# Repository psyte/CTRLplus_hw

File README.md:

# CTRLplus_hw
CTRLplus Eagle schematics and boards

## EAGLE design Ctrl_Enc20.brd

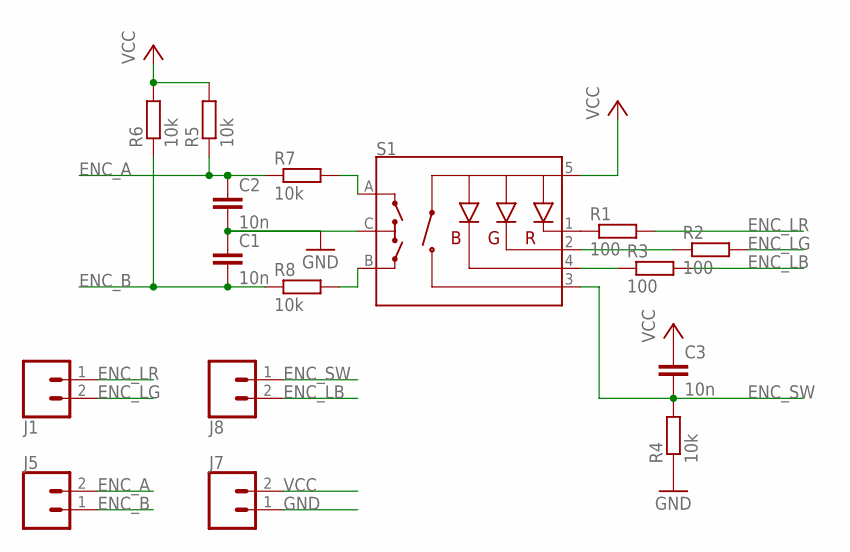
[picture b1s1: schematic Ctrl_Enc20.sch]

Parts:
C1, C2, C3: 10n; C0603
J1, J5, J7, J8: CONN_02; 1X02
R1, R2, R3: 100; R0603
R4, R5, R6, R7, R8: 10k; R0603
S1: ENCODER-RGB-SWITCH; ENCODER_LED_3

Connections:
ENC_A: C2.1, J5.2, R5.1, R7.1
ENC_B: C1.2, J5.1, R6.1, R8.1
ENC_LB: J8.2, R3.2
ENC_LG: J1.2, R2.2
ENC_LR: J1.1, R1.2
ENC_SW: C3.2, J8.1, R4.2, S1.3 (SW)
GND: C1.1, C2.2, J7.1, R4.1, S1.C
unnamed: R1.1, S1.1 (-R)
unnamed: R2.1, S1.2 (-G)
unnamed: R3.1, S1.4 (-B)
unnamed: R7.2, S1.A
unnamed: R8.2, S1.B
VCC: C3.1, J7.2, R5.2, R6.2, S1.5 (+)

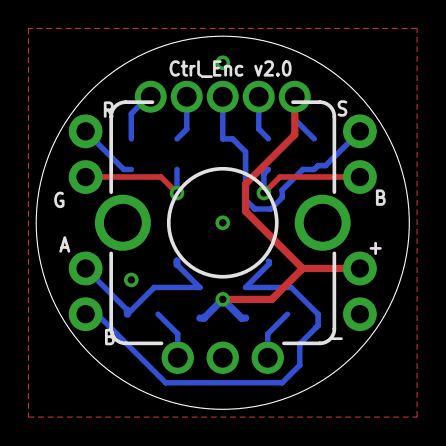
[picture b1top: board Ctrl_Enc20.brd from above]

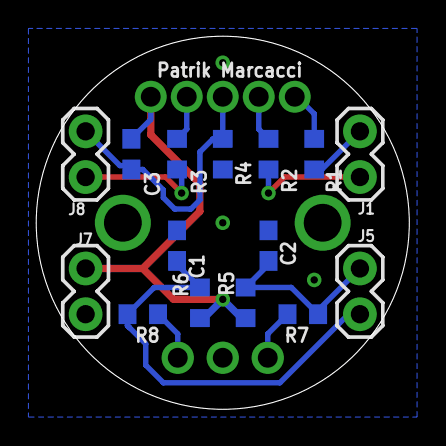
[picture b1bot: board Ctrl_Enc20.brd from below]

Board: 2 copper layers, 20.7 x 20.7 mm, 16 parts (15 on the bottom side), 13 nets.

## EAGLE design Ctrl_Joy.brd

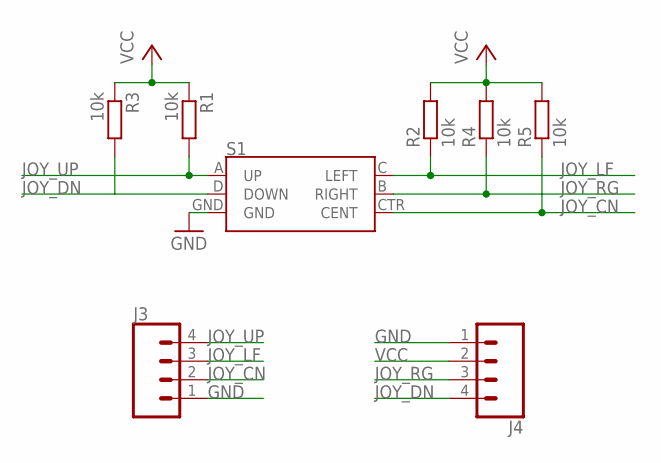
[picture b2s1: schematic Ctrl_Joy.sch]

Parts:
J3, J4: CONN_04; 1X04
R1, R2, R3, R4, R5: 10k; R0603
S1: JOYSTICK_MINI

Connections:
GND: J3.1, J4.1, S1.GND
JOY_CN: J3.2, R5.1, S1.CTR (CENT)
JOY_DN: J4.4, R3.2, S1.D (DOWN)
JOY_LF: J3.3, R2.1, S1.C (LEFT)
JOY_RG: J4.3, R4.1, S1.B (RIGHT)
JOY_UP: J3.4, R1.2, S1.A (UP)
VCC: J4.2, R1.1, R2.2, R3.1, R4.2, R5.2

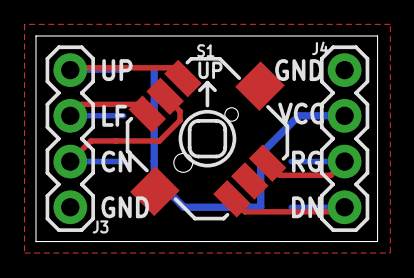
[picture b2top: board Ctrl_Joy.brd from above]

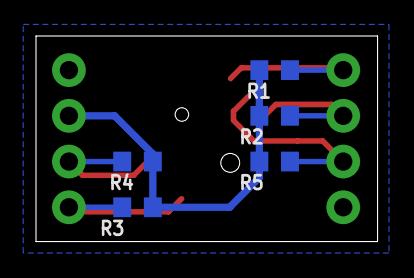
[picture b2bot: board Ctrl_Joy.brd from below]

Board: 2 copper layers, 19.0 x 11.4 mm, 8 parts (5 on the bottom side), 7 nets.

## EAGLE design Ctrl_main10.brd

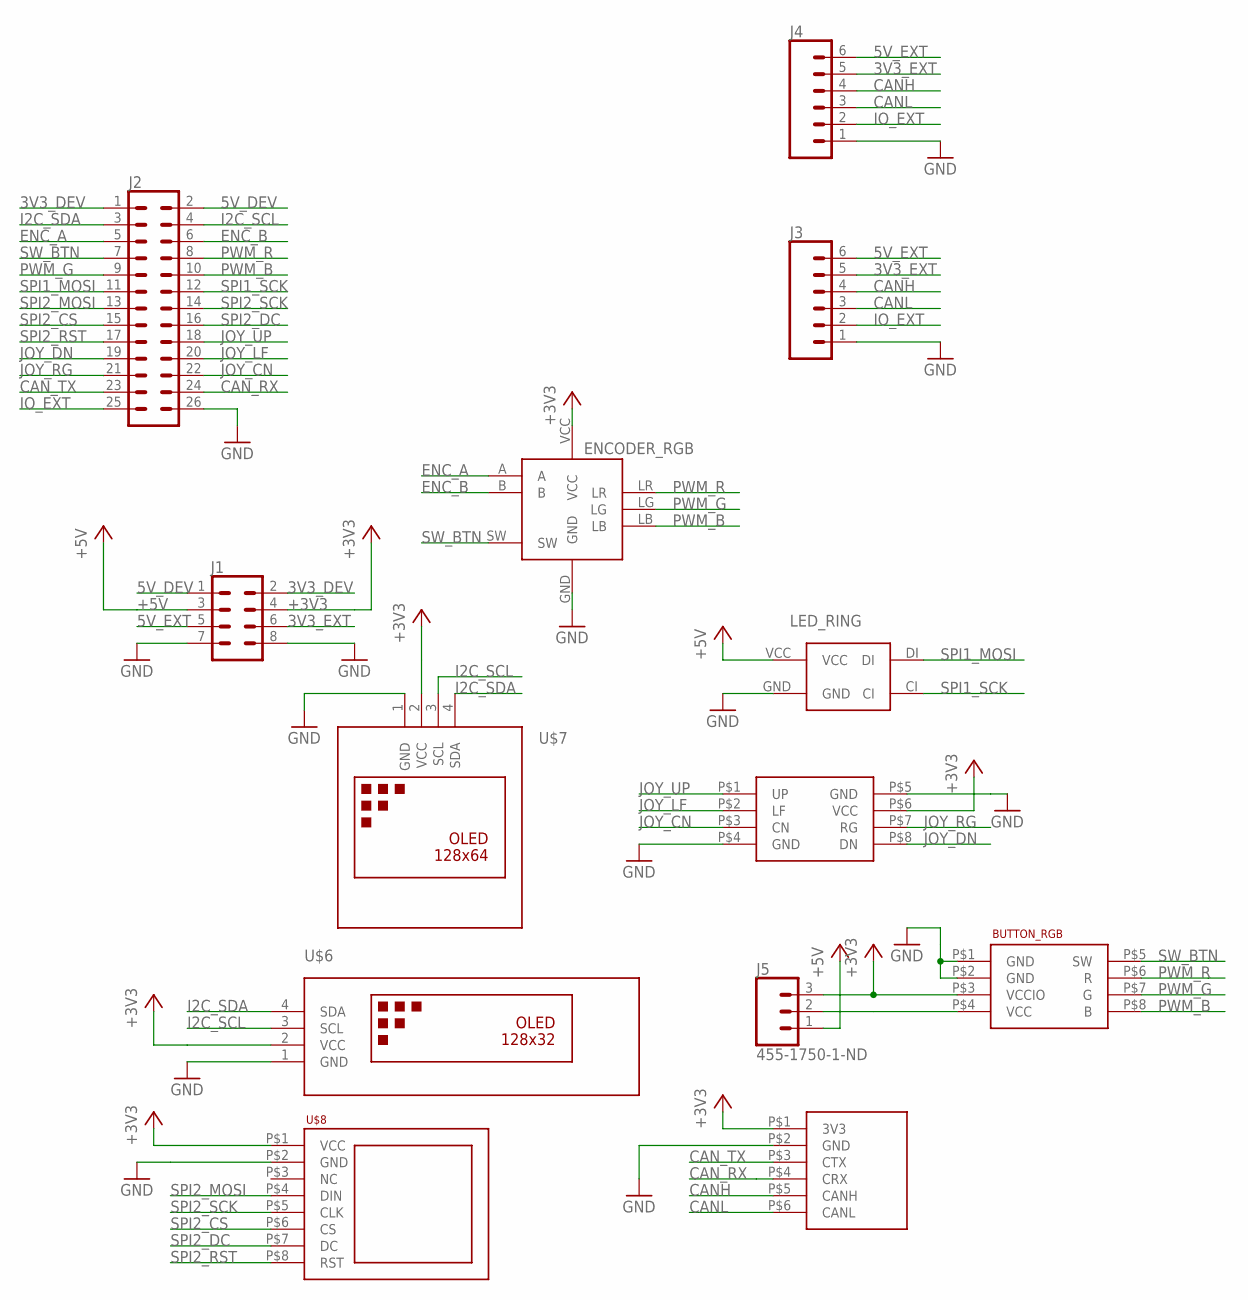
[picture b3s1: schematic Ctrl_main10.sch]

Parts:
BUTTON_RGB: CTRL_BTNRGB_BRD
ENCODER_RGB: CTRL_ENC
J1: CONN_04X2; 2X4
J2: CONN_13X22X13; 2X13
J3, J4: CONN_06SILK_FEMALE_PTH; 1X06
J5: 455-1750-1-ND; 1X03
LED_RING: CTRL_RING
U$3: CTRL_JOY
U$4: CTRL_CAN
U$6: DISPLAY-OLED-128X32
U$7: DISPLAY-OLED-128X64-I2C
U$8: OLED_WS128

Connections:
3V3_DEV: J1.2, J2.1
3V3_EXT: J1.6, J3.5, J4.5
5V_DEV: J1.1, J2.2
5V_EXT: J1.5, J3.6, J4.6
+3V3: BUTTON_RGB.P$3 (VCCIO), ENCODER_RGB.VCC, J1.4, J5.3, U$3.P$6 (VCC), U$4.P$1 (3V3), U$6.2 (VCC), U$7.2 (VCC), U$8.P$1 (VCC)
+5V: J1.3, J5.1, LED_RING.VCC
CANH: J3.4, J4.4, U$4.P$5 (CANH)
CANL: J3.3, J4.3, U$4.P$6 (CANL)
CAN_RX: J2.24, U$4.P$4 (CRX)
CAN_TX: J2.23, U$4.P$3 (CTX)
ENC_A: ENCODER_RGB.A, J2.5
ENC_B: ENCODER_RGB.B, J2.6
GND: BUTTON_RGB.P$1 (GND), BUTTON_RGB.P$2 (GND), ENCODER_RGB.GND, J1.7, J1.8, J2.26, J3.1, J4.1, LED_RING.GND, U$3.P$4 (GND), U$3.P$5 (GND), U$4.P$2 (GND), U$6.1 (GND), U$7.1 (GND), U$8.P$2 (GND)
I2C_SCL: J2.4, U$6.3 (SCL), U$7.3 (SCL)
I2C_SDA: J2.3, U$6.4 (SDA), U$7.4 (SDA)
IO_EXT: J2.25, J3.2, J4.2
JOY_CN: J2.22, U$3.P$3 (CN)
JOY_DN: J2.19, U$3.P$8 (DN)
JOY_LF: J2.20, U$3.P$2 (LF)
JOY_RG: J2.21, U$3.P$7 (RG)
JOY_UP: J2.18, U$3.P$1 (UP)
unnamed: BUTTON_RGB.P$4 (VCC), J5.2
PWM_B: BUTTON_RGB.P$8 (B), ENCODER_RGB.LB, J2.10
PWM_G: BUTTON_RGB.P$7 (G), ENCODER_RGB.LG, J2.9
PWM_R: BUTTON_RGB.P$6 (R), ENCODER_RGB.LR, J2.8
SPI1_MOSI: J2.11, LED_RING.DI
SPI1_SCK: J2.12, LED_RING.CI
SPI2_CS: J2.15, U$8.P$6 (CS)
SPI2_DC: J2.16, U$8.P$7 (DC)
SPI2_MOSI: J2.13, U$8.P$4 (DIN)
SPI2_RST: J2.17, U$8.P$8 (RST)
SPI2_SCK: J2.14, U$8.P$5 (CLK)
SW_BTN: BUTTON_RGB.P$5 (SW), ENCODER_RGB.SW, J2.7

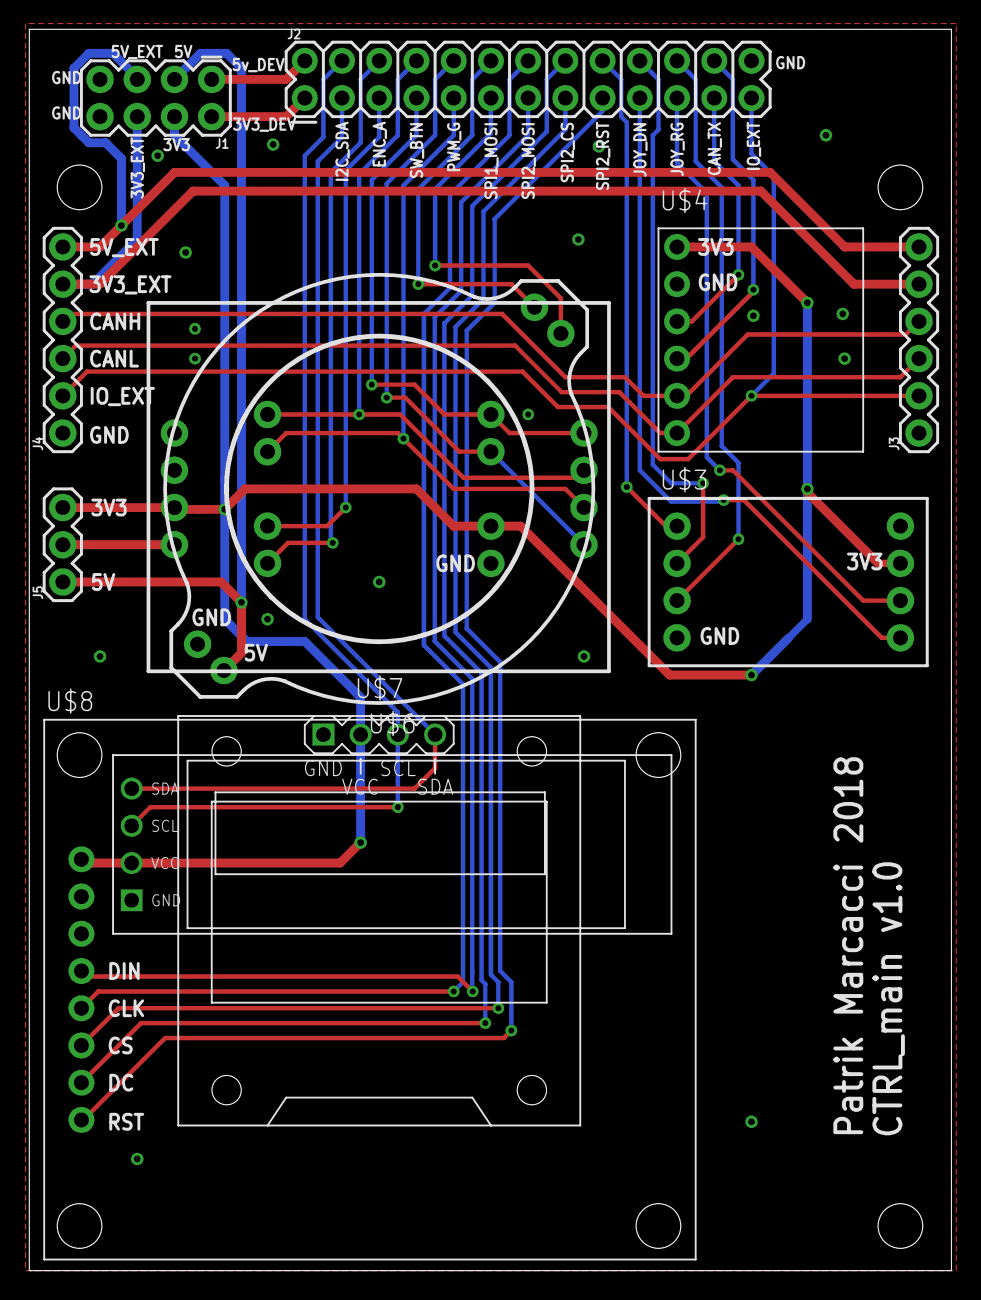
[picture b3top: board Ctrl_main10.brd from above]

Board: 2 copper layers, 62.9 x 84.7 mm, 13 parts (0 on the bottom side), 33 nets.

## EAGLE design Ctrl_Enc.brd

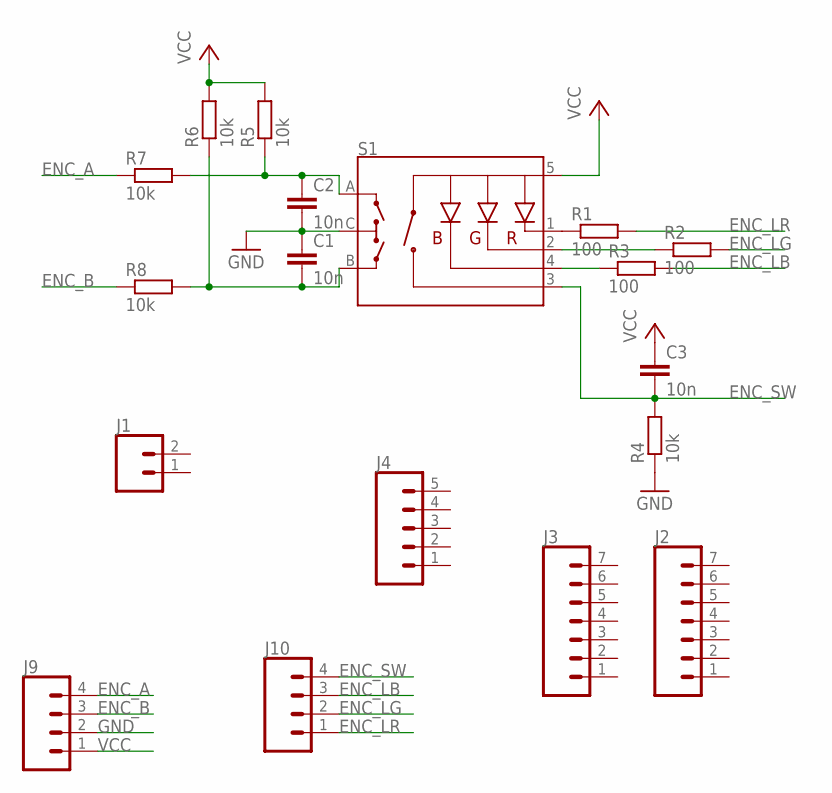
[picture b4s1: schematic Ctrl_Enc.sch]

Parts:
C1, C2, C3: 10n; C0603
J1: CONN_02; 1X02
J2, J3: CONN_07; 1X07
J4: CONN_05; 1X05
J9, J10: CONN_04; 1X04
R1, R2, R3: 100; R0603
R4, R5, R6, R7, R8: 10k; R0603
S1: ENCODER-RGB-SWITCH; ENCODER_LED_3

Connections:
ENC_A: J9.4, R7.1
ENC_B: J9.3, R8.1
ENC_LB: J10.3, R3.2
ENC_LG: J10.2, R2.2
ENC_LR: J10.1, R1.2
ENC_SW: C3.2, J10.4, R4.2, S1.3 (SW)
GND: C1.1, C2.2, J9.2, R4.1, S1.C
unnamed: R1.1, S1.1 (-R)
unnamed: R2.1, S1.2 (-G)
unnamed: R3.1, S1.4 (-B)
unnamed: C1.2, R6.1, R8.2, S1.B
unnamed: C2.1, R5.1, R7.2, S1.A
VCC: C3.1, J9.1, R5.2, R6.2, S1.5 (+)

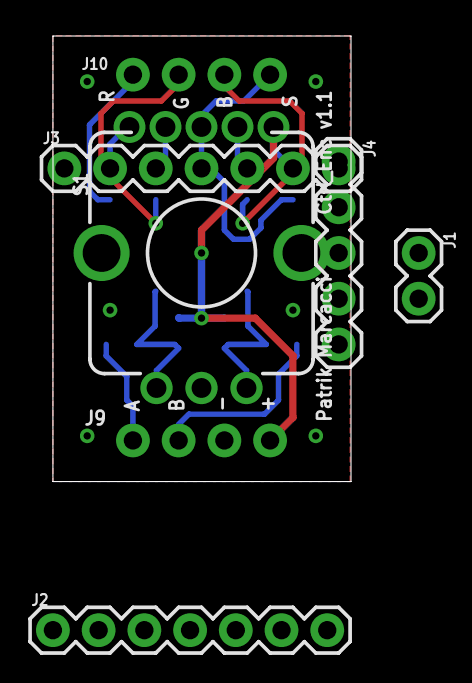
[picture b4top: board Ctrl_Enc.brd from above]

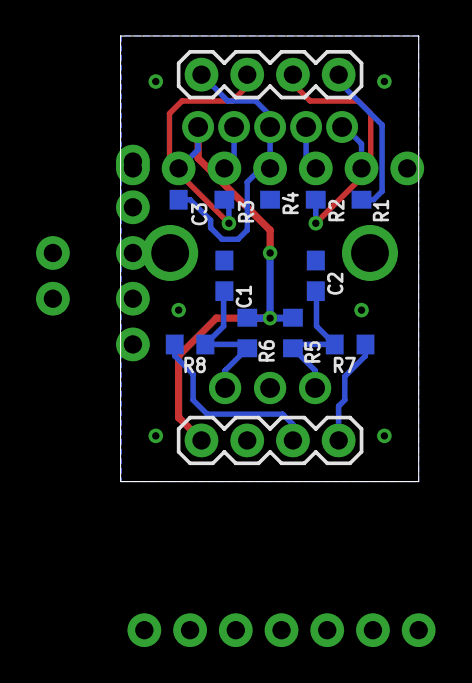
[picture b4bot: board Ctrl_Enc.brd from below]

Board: 2 copper layers, 16.6 x 24.8 mm, 18 parts (13 on the bottom side), 13 nets.

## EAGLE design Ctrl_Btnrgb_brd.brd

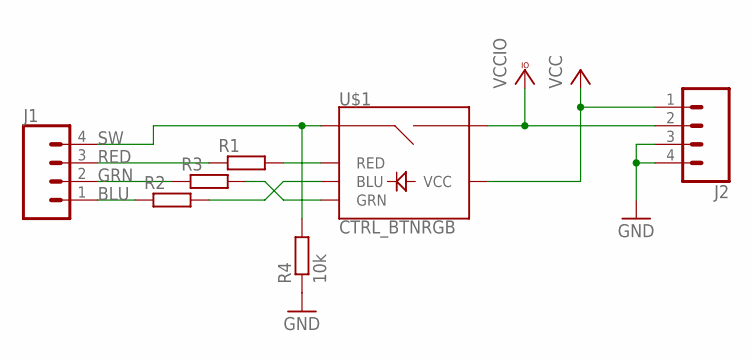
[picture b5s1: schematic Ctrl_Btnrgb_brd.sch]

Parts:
J1, J2: CONN_04; 1X04
R1, R2, R3: R-EU_R0603; R0603
R4: 10k; R0603
U$1: CTRL_BTNRGB

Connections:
BLU: J1.1, R2.1
GND: J2.3, J2.4, R4.1
GRN: J1.2, R3.1
unnamed: R1.2, U$1.RED
unnamed: R2.2, U$1.BLU
unnamed: R3.2, U$1.GRN
RED: J1.3, R1.1
SW: J1.4, R4.2, U$1.SIG1
VCC: J2.1, U$1.VCC
VCCIO: J2.2, U$1.SIG2

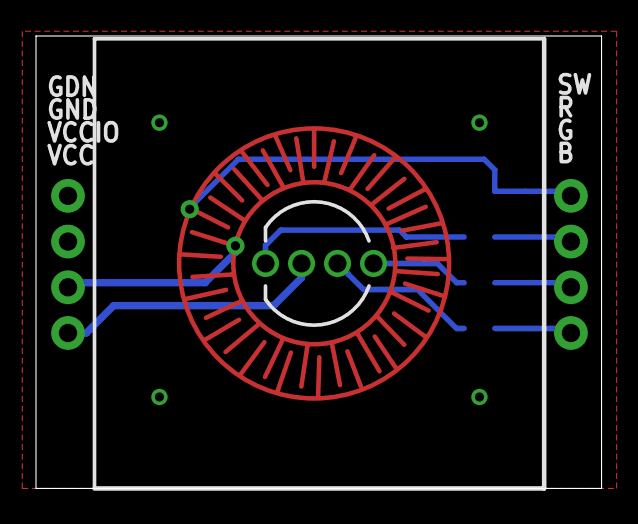
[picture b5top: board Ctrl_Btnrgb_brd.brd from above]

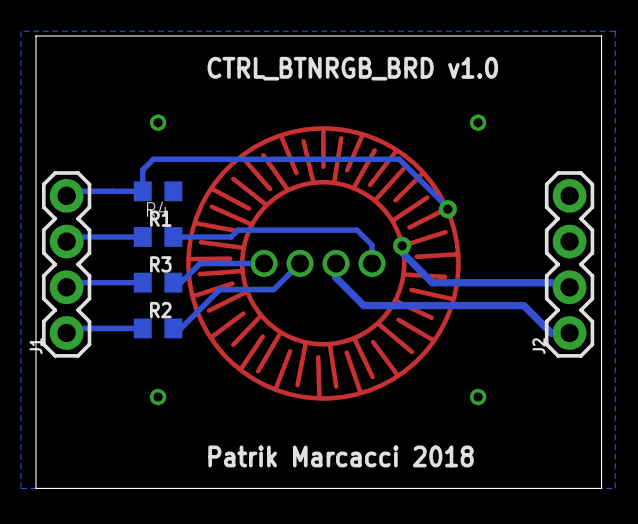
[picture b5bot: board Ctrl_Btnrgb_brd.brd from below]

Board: 2 copper layers, 31.4 x 25.1 mm, 7 parts (6 on the bottom side), 10 nets.

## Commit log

2018-12-03 Add existing brd and sch
2018-12-04 Revert "Delete eagle.epf"
    This reverts commit dd0a26ca01086de3a1a74348a8c65d661061c66b.

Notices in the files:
parts and their libraries:
SparkFun-Connectors: Licensing: Creative Commons ShareAlike 4.0 International - https://creativecommons.org/licenses/by-sa/4.0
diy-modules: Released under the Creative Commons Attribution 4.0 International License: http://creativecommons.org/licenses/by/4.0
